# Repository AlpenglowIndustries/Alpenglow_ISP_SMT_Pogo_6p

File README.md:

# Alpenglow_ISP_SMT_Pogo_6p
6 pin ISP pogo adapter for 0.3" wide SMT footprints

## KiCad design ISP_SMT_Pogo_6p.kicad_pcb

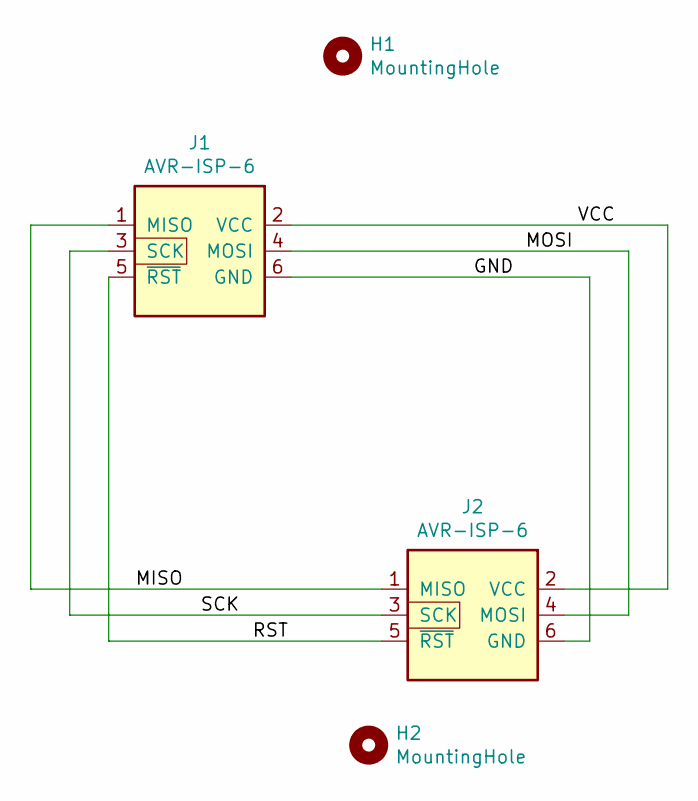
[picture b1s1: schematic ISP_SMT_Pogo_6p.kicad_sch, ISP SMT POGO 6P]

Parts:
H1, H2: MountingHole; MNTG-HOLE-440
J1: AVR-ISP-6; IDC-Header_2x03_P2.54mm_Vertical
J2: AVR-ISP-6; CONN-ISP-Pogo

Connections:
/GND: H1.1, H2.2, J1.6 (GND), J2.6 (GND)
/MISO: J1.1 (MISO), J2.1 (MISO)
/MOSI: J1.4 (MOSI), J2.4 (MOSI)
/RST: J1.5 (~RST), J2.5 (~RST)
/SCK: J1.3 (SCK), J2.3 (SCK)
/VCC: J1.2 (VCC), J2.2 (VCC)

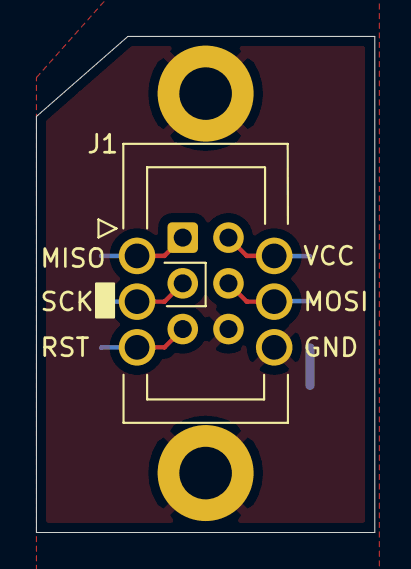
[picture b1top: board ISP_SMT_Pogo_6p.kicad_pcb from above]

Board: 2 copper layers, 18.8 x 27.6 mm, 4 parts (0 on the bottom side), 6 nets.

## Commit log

2022-10-24 Shematic PDF
2022-10-26 Moved gerbers to folder, BOM
2022-10-27 Updated gitignore, changed BOM to CSV file
